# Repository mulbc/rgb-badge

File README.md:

<!-- SPDX-License-Identifier: CERN-OHL-S-2.0 -->

**2026-11-20 selected — 22 opens:** The [additive PAIR03 supply join](docs/development/pair03-supply-routing-2026-11-20.md) preserves all 211 previous groups and all 19,349 existing copper items, with GND197/VLED39/USB32. Matching native/physical counts, exact original 104 findings, stable independent replays, byte-exact inverse/nine zone XORs, 32 fault rejections, eight hole controls, 43 source checks and native visual review pass. Use `led-pair03-supply-routing-trial-114mm`. Zero opens and all qualification/Gate A holds remain unfinished; fabrication is prohibited.

**2026-11-24 continuation — selected source remains22 opens:** The [front row-cell discovery](docs/development/front-row-cell-discovery-2026-11-24.md) preserves a repository-replayable three-part cell and independently restored selector. Its21-open RAM state still splits ROW04 and is explicitly unselected. Actual-contact and alternate-placement escapes continue; no successor PCB or fabrication release is selected.

**2026-11-20 selected — 23 opens:** The [PAIR01 supply continuation](docs/development/pair01-supply-routing-2026-11-20.md) joins PAIR01.4 to main VLED38, preserving all 212 prior groups, main GND197 and retained attached copper. Native and physical counts match at23 with exact original104. Replays, byte-exact inverse/all nine zone XORs, 43 fault/hole/courtyard controls, 42 source checks and native visual review pass. Use `led-pair01-supply-routing-trial-114mm`. Zero opens and all qualification/Gate A holds remain unfinished; fabrication is prohibited.

**2026-11-20 selected — 24 opens:** The [R6 direct bottom continuation](docs/development/r6-direct-bottom-routing-2026-11-20.md) preserves all 213 prior groups, all 197 main ground pads, all 37 main VLED pads and attached retained copper. Native and physical counts match at 24 with exact original104. Replays, byte-exact inverse/all nine zone XORs, 43 fault/hole/courtyard controls, 41 source checks and native visual review pass. Use `led-r6-direct-bottom-trial-114mm`. Zero opens and all qualification/Gate A holds remain unfinished; fabrication is prohibited.

**2026-11-19 selected — 27 opens:** The [minimal R21 supply join](docs/development/r21-routing-2026-11-19.md) preserves all 216 prior groups and attached source copper, with 27 matching native/physical opens and exact original104. Exact replays/inverse, serialized-source guards, 28 fault rejections, eight hole controls, 38 source checks and native visual review pass. Use `led-r21-routing-trial-114mm`; the zero-open goal and all qualification/Gate A holds remain unfinished. Fabrication is prohibited.

**2026-11-15 selected — 29 opens:** The [inverter clock join](docs/development/inverter-routing-2026-11-15.md) localizes exact U48/C67 and joins U48.4–U49.7. All 218 prior groups survive. Native/physical 29 opens, exact original 104 findings under independent U48/prior U52 transforms, two byte-identical replays, byte-identical inverse reconstruction, 18 fault guards, eight hole-policy controls, 36 source checks and visual review pass. Use `led-inverter-routing-trial-114mm`. Zero opens and all electrical/part/process/fit/stack/Gate A holds remain; fabrication is prohibited.

**2026-11-14 selected — 30 opens:** The [complete enable join](docs/development/enable-routing-2026-11-14.md) closes the five-terminal DISPLAY_ENABLE group with one exact C71 shift and two private-leaf replacements. All 219 prior groups survive. Native/physical 30 opens, exact original 104 findings under the unchanged prior pose transform, stable independent replays, inverse-source proof, 18 fault guards, 35 source checks and native visual review pass. Use `led-enable-routing-trial-114mm`. Zero opens and all electrical/part/process/fit/stack/Gate A holds remain; fabrication is prohibited.

**2026-11-14 selected — 31 opens:** The [clear-output join](docs/development/clear-output-routing-2026-11-14.md) connects U52.4 to U49.2/R108.1 through ordinary-width copper. All 220 prior groups and 19,226 source copper items survive. Native/physical 31 opens, exact original 104 finding payloads under the existing frozen pose transform, independent stable replays, byte-identical source restoration, eleven native faults, 34 source checks and native visual review pass. Use `led-ordinary-routing-trial-114mm`. Zero opens and electrical/part/process/fit/stack/Gate A acceptance remain unresolved; fabrication is prohibited.

**2026-11-14 selected — 32 opens:** The [complete control cluster](docs/development/control-cluster-routing-2026-11-14.md) joins U51.4–U52.1 with exact U52/C71 placement and bounded loop/row replacements. All 221 original groups survive, with 32 native/physical opens, the original 104 finding payloads under the exact U52 pose transform, stable byte-identical replays, inverse-source proof, 18 fault guards, 33 source checks and native visual review. Use `led-control-cluster-routing-trial-114mm`. Zero opens, electrical/part/process/fit/stack qualification and independent Gate A remain open; fabrication is prohibited.

**2026-11-12 selected — 33 opens:** The [gauge-supply join](docs/development/gauge-supply-routing-2026-11-12.md) adds exact ordinary-width copper, preserving every prior group and source item. Native/physical 33 opens, exact unchanged 104 findings, stable byte-identical replays, eleven native faults, 32 source checks and visual review pass. Use `led-gauge-routing-trial-114mm`. U35 supply, zero opens and electrical/process/fit/stack/Gate A acceptance remain open; fabrication is prohibited.

**2026-11-12 selected — 34 opens:** The [USB EN1 join](docs/development/usb-en1-routing-2026-11-12.md) localizes exact R70/TP31 and joins U23.4, preserving every prior group and all other copper with no new vias. Exact unchanged 104 findings, stable independent replays, 12 native faults, 31 source checks and visual review pass. Use `led-usb-en1-routing-trial-114mm`; the corrected RSE parent stays immutable. Zero opens and electrical/process/fit/stack/Gate A acceptance remain open; fabrication is prohibited.

**2026-11-12 corrected routing source — 35 opens:** The [RSE pin correction](docs/development/rse-pin-correction-2026-11-12.md) fixes U49/U50 physical pin assignments, restores all 223 prior functional groups and preserves all previous accepted additions. Exact unchanged 104 findings, independent stable replays, native/source/fault and visual checks pass. Continue from `led-rse-corrected-routing-trial-114mm`; preceding boards retain the historical wrong map. Zero opens, electrical/process/fit/stack qualification and independent Gate A remain open; fabrication is prohibited.

**2026-11-07 switch routing selected — 43 opens:** The [validated successor](docs/development/switch-routing-2026-11-07.md) joins SW2.3–R83.1–U36.5, retains all 232 immutable 44-open parent groups and every prior copper item, and passes exact unchanged 104-finding DRC, stable replay/fills, source/orphan/fault and visual checks. The zero-open goal remains in progress. Added supply bridges, controlled stack, 557 historical centre microvias, electrical/process/fit qualification and independent Gate A remain open; fabrication is prohibited.

**2026-11-09 remaining routing selected — 36 opens:** The [validated successor](docs/development/remaining-routing-2026-11-07.md) shifts exact C32 upward by 0.250 mm, retaining its supply contact and joining its ground island through one filled B.Cu component. No copper is added or retired by this step. All 225 preceding groups and 226 additions, plus all 231 immutable parent groups, survive. Exact unchanged 104-finding DRC, stable replay/fills, 36 fault guards, 27 source checks and native visual review pass. The zero-open goal, electrical/thermal/stack/process/fit qualification, 557 historical centre vias and independent Gate A remain open; fabrication is prohibited.
# RGB Badge

An open-source, full-colour wearable LED badge inspired by the FOSSASIA Badge Magic form factor.

The project is currently in **draft schematic development**. Several coupon circuits are captured, including a provisional charger core, but the complete power circuit and PCB are unfinished. No board in this repository has been independently reviewed, fabricated or tested. Do not treat current design material as production-ready.

The current [30-open CAD study](docs/development/enable-routing-2026-11-14.md) retains 104 inventoried intrinsic findings. Circuit completion, electrical/process/fit/stack qualification and independent Gate A review remain open.

## Product target

| Property | Target |
|---|---:|
| Display | 48 × 16 individually controlled RGB pixels |
| Pixel pitch | 1.95 mm |
| Finished envelope | ≤118 × 35 × 11 mm working limit; 114 × 32.5 mm PCB target |
| Finished weight | ≤75 g target; 100 g absolute maximum |
| Reference runtime | Approximately 6 h at the defined mixed-content workload and fixed indoor brightness |
| Charging/data | USB-C, 5 V, A-to-C and C-to-C; native USB data |
| Wireless | BLE enabled only in programming mode |
| Controller | ESP32-S3-WROOM-1U-N16R8 |
| Manufacturing | Turnkey PCBA; no hand assembly of SMT parts |

Six hours is not a maximum-brightness guarantee. The initial model predicts about 6.3 hours with a 900 mAh cell for the reference workload and about 1.1 hours for continuous maximum full-screen white. Coupon measurements will replace those estimates.

## Development strategy

The first physical board is a production-intent 16 × 16 coupon. It compares Everlight `EAST10105RGBA0` 1010 and QT Brightek `QBLP1515A-RGB2A` 1515 common-anode RGB LEDs while exercising the intended controller, matrix driver, USB-C, charger, battery gauge, power converters, antenna and controls. The full 48 × 16 badge will not be ordered until the coupon passes its electrical, optical, thermal, runtime and RF acceptance tests.

For coupon routing, [ADR 0034](docs/decisions/0034-uniform-qt-coupon-pitch-proposal.md) sets the 1515 half to 2.2 mm horizontal / 1.95 mm vertical pitch and uniform orientation; the 1010 half stays at 1.95 mm in both axes. The final badge still targets no more than 1.95 mm in either axis, so coupon optical comparisons must account for the different spacing.

Start with:

1. [Project context](CONTEXT.md)
2. [Requirements](docs/requirements.md)
3. [Full project plan](docs/project-plan.md)
4. [Accepted decisions](docs/decisions/README.md)
5. [Coupon core component candidates](docs/sourcing/coupon-rev-a-core-candidates.md)
6. [Contributor and agent rules](AGENTS.md)

## Repository layout

| Path | Contents |
|---|---|
| `docs/` | Requirements, decisions, project plan, bring-up and test evidence |
| `hardware/` | Editable KiCad projects and project-local libraries |
| `firmware/` | ESP-IDF firmware and host-side tests |
| `mechanical/` | Parametric enclosure source and reviewed exports |
| `manufacturing/` | Immutable, revisioned fabrication and assembly releases |
| `tools/` | Asset compiler, validation and release tooling |

## Safety and verification

This project contains a rechargeable lithium-polymer cell and switching power electronics. A completed coupon schematic and preliminary PCB layout must be reviewed by an experienced hardware engineer before fabrication. Battery charge limits may only be changed after checking the exact terminated-pack specification. Test results must always identify the board revision and must never be inferred or fabricated.

## Attribution

The project uses the [FOSSASIA Badge Magic hardware](https://github.com/fossasia/badgemagic-hardware) as an attributed reference. It is a new design rather than a copy of that PCB. See [NOTICE](NOTICE).

## Licensing

- Hardware design files, mechanical design files, manufacturing files and hardware documentation: [CERN-OHL-S-2.0](LICENSES/CERN-OHL-S-2.0.txt).
- Firmware, scripts and software tooling: [Apache-2.0](LICENSES/Apache-2.0.txt).
- Third-party files retain their original licences and must be recorded before inclusion.

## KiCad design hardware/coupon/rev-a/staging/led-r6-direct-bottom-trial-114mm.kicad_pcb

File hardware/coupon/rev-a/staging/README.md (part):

<!-- SPDX-License-Identifier: CERN-OHL-S-2.0 -->

**2026-11-15 selected — 28 opens:** The [complete row-two exchange](../../../../docs/development/row2-routing-2026-11-15.md) moves exact R8/R37, joins the full ROW_GATE_02 and restores all selector/ground contacts. All 217 prior groups survive, with matching native/physical counts and exact original 104 findings. Two byte-identical replays, byte-identical inverse, 21 fault guards, eight hole controls, 37 source checks and native visual review pass. Use `led-row2-routing-trial-114mm`. Zero opens and all electrical/part/process/fit/stack/Gate A holds remain; fabrication is prohibited.

Current routed derivative: [58-edge source with printed switch terminals](led-routing-progress-trial-114mm.kicad_pcb). The [source record](../../../../docs/development/led-routing-progress-58-study-2026-10-30.md) preserves all earlier physical groups/copper/poses and the 104 intrinsic findings, corrects the second-pole labels without moving contacts, and adds the exact gauge-switch supply join. Run `./tools/check-routing-progress.sh`. Inductor locality, electrical/assembly qualification and independent Gate A remain open; fabrication is prohibited.

Historical routed derivative: [native-clearance gate/control continuation](../../../../docs/development/led-native-control-study-2026-10-21.md)
records nineteen joins and exact retirement of twenty-five source tracks/four vias across ROW_SEL_04/COL_07_R/COL_06_G/COL_02_G, with
no placement changes, leaving 215 native opens and the
same 104 intrinsic DRC findings. Run `./tools/check-native-control.sh` from the
repository root. All prior physical pad groups survive; electrical/process/fit
qualification and Gate A remain open. Never fabricate from this study.

Preceding routed derivative: [row-13 bias study](../../../../docs/development/led-row13-bias-study-2026-10-21.md)
moves R19 and joins its gate/VLED terminals, leaving 234 native opens and the
same 104 intrinsic DRC findings. Existing copper and pad groups survive; nine
gate-side pullups connect. Run `./tools/check-row13-bias.sh` from the repository
root. This mixed-source, unbuilt study is never fabrication source.

# Coupon staging and layout studies

**Historical combined routing study:** The [guarded control continuation](led-control-continuation-trial-114mm.kicad_pcb) has 236 native opens and exactly 104 unchanged intrinsic DRC findings. [Evidence](../../../../docs/development/led-control-continuation-study-2026-10-21.md) records ten joins, preserved existing physical pad groups and rollback of plane-splitting routes. Run `./tools/check-control-continuation.sh` from the repository root. No component, current setting or display-output boundary changes; this unbuilt mixed-source study is never fabrication source.

**Previous physical-drain checkpoint:** [Both physical row-drain lands](led-row-drain-tie-trial-114mm.kicad_pcb) are now joined on all sixteen pairs. [Evidence](../../../../docs/development/led-row-drain-tie-study-2026-10-20.md) records 246 native opens, unchanged source tracks/placements/other pad clusters, exactly 104 intrinsic DRC findings, deterministic regeneration and a negative missing-tie test. Run `./tools/check-row-drain-tie.sh` from the repository root. This unbuilt mixed-source study is never fabrication source.

The separate [VLED converter candidate](../vled-converter-capture-contract.md) now stages thirteen exact-MPN items in vled-converter.kicad_sch. It is default-disabled and remains unlinked until protected SYS and the hardware display interlock are captured.

The separate [VLED local layout trial](vled-layout-trial.kicad_pcb) uses the same thirteen project-local footprints and their exported schematic pad nets at the coordinates of the [lower-right cluster screen](../../../../mechanical/dual-row-package-screen-2026-10-06.md). It has a local study outline, no tracks, vias or copper zones, and none of the neighbouring final-board circuitry. Generate and round-trip-check it with KiCad's bundled Python: `/Applications/KiCad/KiCad.app/Contents/Frameworks/Python.framework/Versions/3.9/bin/python3 tools/generate-vled-layout-trial.py`. KiCad 10.0.6 loaded and plotted its actual pads. [Native local-board DRC evidence](../../../../docs/development/vled-layout-trial-2026-10-06.md) records zero geometric violations and thirty expected open connections when run with desktop access. This is not a routed/full-board DRC pass. This file is a placement study, never a fabrication source.

The separate [display-interlock placement trial](display-interlock-layout-trial.kicad_pcb) groups the 31 captured interlock footprints and carries their exported pad nets. Generate it with KiCad's bundled Python using `tools/generate-display-interlock-layout-trial.py`. [Native DRC findings](../../../../docs/development/display-interlock-layout-trial-2026-10-13.md) show eight intra-footprint clearance violations at the present 0.20 mm rule and 76 expected unrouted connections. It has no routed/full-board DRC pass and is never a fabrication source.

The [full-footprint 120 mm coupon trial](full-coupon-placement-trial-120mm.kicad_pcb) stages every captured footprint and native pad net on two faces of a provisional six-layer board while retaining all 32 current row transistors. The linked study paths include four E0/E1 support nets, both J1 VBUS pads to E0/C60, E0-to-C61, E1-to-C52, C52-to-U41/C56, the local R93 ILIM/ground loop, C62/C57 timing-capacitor and both eFuse IC ground returns, the second J1 GND contact, E1 pad 2, two U37-to-L2 switching nets and 16 Everlight half-row anode trunks. Nearly all other routing remains open. Its [source and DRC record](../../../../docs/development/full-coupon-placement-trial-2026-10-13.md) explains why this larger board is a layout discovery artifact, not the accepted 110 mm badge PCB or a release output.

The separate [red-column HDI trial](red-column-hdi-trial-120mm.kicad_pcb) copies that full-footprint study and adds tentative pad-centred F.Cu–In1.Cu microvias for all sixteen red cathode columns. [Its review](../../../../docs/development/red-column-hdi-screen-2026-10-14.md) records native DRC and the still-open green/blue routing and manufacturing process. Generate it with `tools/generate-red-column-hdi-trial.py`; it is not the canonical PCB or a fabrication source.

The [114 mm grouped placement study](paired-charger-placement-only-114mm.kicad_pcb) uses actual KiCad pads for the provisional paired-row and charger-group XY option, with two projected final drivers and TH1/U39 fixed in the battery-facing central sensor reservation. It is unrouted and the row-pair/extra-driver pads are netless. [Its native DRC record](../../../../docs/development/paired-charger-114mm-placement-study-2026-10-14.md) identifies 104 known fine-pitch pad-gap violations and a capped unconnected listing; it does not approve the row substitution, sensor thermal coupling, enclosure fit or fabrication. Generate it with `tools/generate-paired-charger-114mm-placement.py` using KiCad's bundled Python.

The separate [114 mm local routing trial](paired-charger-local-routing-trial-114mm.kicad_pcb) connects five BQ24074 support nets, stages three USB-to-charger rail segments (J1 to E0, E0 to E1, E1 to BQ IN) and joins a partial local ground tree. [Its native DRC record](../../../../docs/development/paired-charger-114mm-local-routing-2026-10-14.md) retains the same 104 intrinsic pad-gap findings. The 0.20 mm traces are not qualified for charger/system current, and almost all nets remain open. Generate it with `tools/generate-paired-charger-114mm-routing.py` using KiCad's bundled Python.

`3v3-converter.kicad_sch` contains the exact `TPS631000DRLR`, one Murata `DFE252012P-1R0M=P2` 1 µH inductor, two `GRM187R61A226ME15` input capacitors, two `GRM219R60J476ME44` output capacitors, the Panasonic 511 kΩ / 91 kΩ feedback pair, and a 100 kΩ EN pull-down. The source checker verifies nine items, all 24 pins and the two *local* LX switching nodes. Regenerate deterministically into a new directory with `python3 tools/generate-coupon-3v3.py --output /tmp/rgb-3v3-candidate`; compare with this source before replacing it.

This historical candidate remains **unlinked** for deterministic comparison. A distinct, root-linked copy now exists at `../3v3-converter.kicad_sch` with SW2's first control pole on EN; the previous `+3V3_APP` draft source flag was removed. `+SYS_APP_IN_DRAFT` remains a flagged, unresolved charger/pack source. `APP_3V3_FB` is a schematic feedback net, not a routed board design. The battery pack, charger, gauge pole, LED supply and whole-board OFF leakage remain uncaptured or unqualified.

The [capture contract](../3v3-converter-capture-contract.md) records the TI starting circuit, conditional capacitor choice and load/current sensitivity. The [inductor audit](../3v3-inductor-footprint-audit.md) and capacitor/feedback audits control the libraries. [Native XML and visual review at c929711](../../../../docs/development/3v3-candidate-review-c929711.md) confirms all 24 connections and identifies two presentation repairs, now source-corrected but awaiting the next combined export. No candidate ERC report was supplied; the main project's passing ERC does not validate it. Integrate only after the protected SYS and switch boundaries are reviewed, then remove the superseded flags, run native ERC/netlist and inspect the page, and update the whole-project checker. This is not a fabrication release.

The [combined-board ground-escape candidate](led-ground-escape-trial-114mm.kicad_pcb) adds rear-pad escapes and an In2 GND pour to the combined row-control derivative. [Its evidence and limitations](../../../../docs/development/led-ground-escape-study-2026-10-20.md) record 383 native open edges, six ground regions, unchanged non-ground connectivity and a passing native shape-clearance screen. **Full native DRC completed with desktop access: exactly 104 unchanged intrinsic footprint-clearance findings.** Run `./tools/check-ground-escape.sh` from the repository root for full acceptance. It is never fabrication source.

The [combined-board ground-return derivative](led-ground-return-trial-114mm.kicad_pcb) retains the checked ground escapes and adds rear GND copper plus four targeted joins. [Its native evidence](../../../../docs/development/led-ground-return-study-2026-10-20.md) records 366 total opens, 27 GND opens, exactly 104 unchanged intrinsic DRC findings, unchanged components/non-ground clusters and byte-identical regeneration. Repeat full acceptance with `./tools/check-ground-return.sh` from the repository root. Ground and other routing, RF/thermal/process qualification and independent Gate A remain incomplete; it is never fabrication source.

The [local row-14 bias derivative](led-row14-bias-trial-114mm.kicad_pcb) moves R20 beside PAIR15 and connects both its gate and local VLED terminals. [Native evidence](../../../../docs/development/led-row14-bias-study-2026-10-20.md) records 364 full opens, eight connected gate pullups and exactly 104 unchanged DRC findings. All other components/clusters and source tracks survive; GND still has 27 opens. It is never fabrication source.

The preceding local-control derivative is [local control routing](led-local-control-trial-114mm.kicad_pcb). [Its evidence](../../../../docs/development/led-local-control-study-2026-10-20.md) records ten control joins, 354 full native opens and exactly 104 unchanged intrinsic DRC findings. It preserves all prior placements, tracks/vias and connected pad clusters, including the incomplete ground returns. Repeat full study acceptance with `./tools/check-local-control.sh`. Remaining supplies, eight pullups, HDI/electrical/mechanical qualification and Gate A remain open; it is never fabrication source.

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
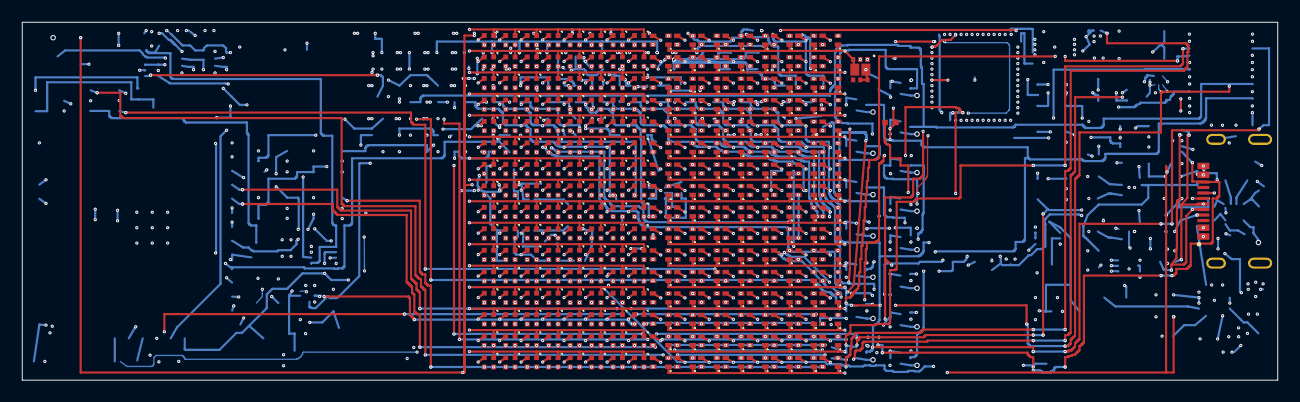
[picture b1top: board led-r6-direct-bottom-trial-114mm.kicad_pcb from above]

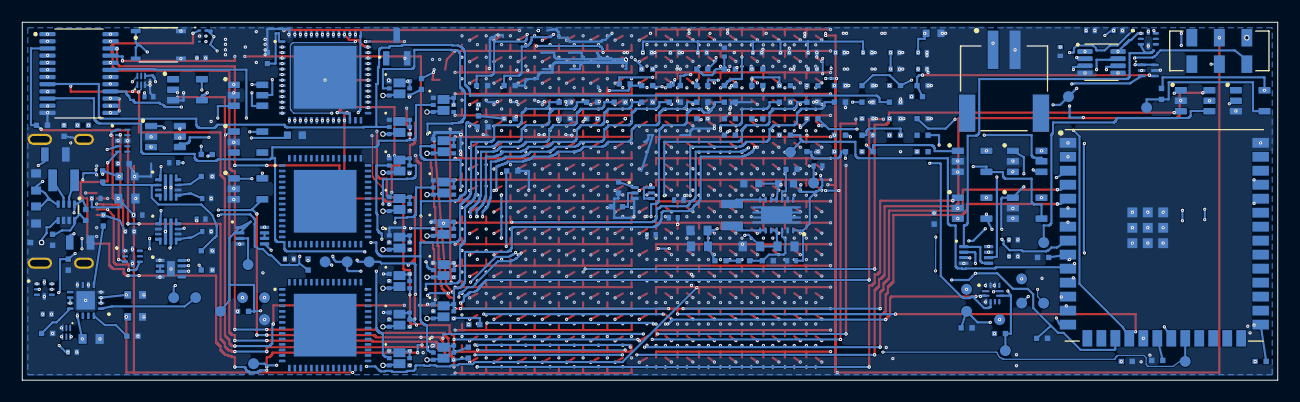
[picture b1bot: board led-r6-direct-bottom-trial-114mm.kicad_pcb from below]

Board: 6 copper layers, 114.0 x 32.5 mm, 483 parts (224 on the bottom side), 188 nets.

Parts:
C1, C2, C4, C11, C17, C23, C24, C25, C36, C37, C38, C39, C50, C51, C55, C58, C59, C63, C64, C65, C66, C67, C68, C69, C70, C71, C72, C73, C74: 100n 16V X7R; C_Murata_GRM15_0402
C3, C32, C44, C45, C53, C54: 10u 6.3V X5R; C_Murata_GRM188R60J106ME47_0603
C5, C30, C31, C52: 1u 10V X7S; C_Murata_GRM15_0402
C40, C41, C46, C47, C48, C49, C56, C61: 22u 10V X5R; C_Murata_GRM187R61A226ME15_0603
C42, C43: 47u 6.3V X5R; C_Murata_GRM219R60J476ME44_0805
C57, C62: 2.2n 50V C0G; C_Murata_GRM15_0402
C60: 1u 50V X7R; C_TDK_C1608_0603
D1, D2, D3, D4, D5, D6, D7, D8, D17, D18, D19, D20, D21, D22, D23, D24, D33, D34, D35, D36, D37, D38, D39, D40, D49, D50, D51, D52, D53, D54, D55, D56, D65, D66, D67, D68, D69, D70, D71, D72, D81, D82, D83, D84, D85, D86, D87, D88, D97, D98, D99, D100, D101, D102, D103, D104, D113, D114, D115, D116, D117, D118, D119, D120, D129, D130, D131, D132, D133, D134, D135, D136, D145, D146, D147, D148, D149, D150, D151, D152, D161, D162, D163, D164, D165, D166, D167, D168, D177, D178, D179, D180, D181, D182, D183, D184, D193, D194, D195, D196, D197, D198, D199, D200, D209, D210, D211, D212, D213, D214, D215, D216, D225, D226, D227, D228, D229, D230, D231, D232, D241, D242, D243, D244, D245, D246, D247, D248: EAST10105RGBA0; LED_Everlight_EAST10105RGBA0
D9, D10, D11, D12, D13, D14, D15, D16, D25, D26, D27, D28, D29, D30, D31, D32, D41, D42, D43, D44, D45, D46, D47, D48, D57, D58, D59, D60, D61, D62, D63, D64, D73, D74, D75, D76, D77, D78, D79, D80, D89, D90, D91, D92, D93, D94, D95, D96, D105, D106, D107, D108, D109, D110, D111, D112, D121, D122, D123, D124, D125, D126, D127, D128, D137, D138, D139, D140, D141, D142, D143, D144, D153, D154, D155, D156, D157, D158, D159, D160, D169, D170, D171, D172, D173, D174, D175, D176, D185, D186, D187, D188, D189, D190, D191, D192, D201, D202, D203, D204, D205, D206, D207, D208, D217, D218, D219, D220, D221, D222, D223, D224, D233, D234, D235, D236, D237, D238, D239, D240, D249, D250, D251, D252, D253, D254, D255, D256: QBLP1515A-RGB2A; LED_QTBrightek_QBLP1515A-RGB2A
J1: USB4505-03-0-A; USB_C_GCT_USB4505-03-0-A_MidMount
J2: S2B-PH-SM4-TB; JST_PH_S2B-PH-SM4-TB
L1: 1u 20%; L_Murata_DFE252012P
L2: 1.5u 20%; L_Murata_DFE252012P
PAIR01, PAIR02, PAIR03, PAIR04, PAIR05, PAIR06, PAIR07, PAIR08, PAIR09, PAIR10, PAIR11, PAIR12, PAIR13, PAIR14, PAIR15, PAIR16: NTLJD3119CTBG_TRIAL_ONLY; WDFN6_2x2_onsemi_NTLJD3119C
PROJ_U1_2, PROJ_U1_3: PROJECTED_DRIVER_GEOMETRY_ONLY; QFN_TI_RTQ0056E_8x8mm_P0.5mm_EP5.7mm
R1: 39.2k 1%; R_Panasonic_ERJ2_0402
R2, R3, R4, R5, R22, R23, R24, R25, R26, R27, R28, R29, R30, R31, R32, R33, R34, R35, R36, R37, R38, R39, R40, R41, R42, R62, R76, R77, R78, R83, R87: 100k 1%; R_Panasonic_ERJ2_0402
R6, R7, R8, R9, R10, R11, R12, R13, R14, R15, R16, R17, R18, R19, R20, R21: 1k 1%; R_Panasonic_ERJ2_0402
R43, R44, R60, R61, R70, R88, R91, R98: 10k 1%; R_Panasonic_ERJ2_0402
R45, R46: 22R 1%; R_Panasonic_ERJ2_0402
R47: 499R 1%; R_Panasonic_ERJ2_0402
R63: 1M 1%; R_Panasonic_ERJ2_0402
R71: 887k 1%; R_Panasonic_ERJ2_0402
R75, R84, R85: 620k 1%; R_Panasonic_ERJ2_0402
R79, R80, R101, R102: 2.2k 1%; R_Panasonic_ERJ2_0402
R81: 511k 1%; R_Panasonic_ERJ2_0402
R82: 91k 1%; R_Panasonic_ERJ2_0402
R86: 180k 1%; R_Panasonic_ERJ2_0402
R89: 2.15k 1%; R_Panasonic_ERJ2_0402
R90: 14k 1%; R_Panasonic_ERJ2_0402
R92: 2.49k 0.1%; R_Panasonic_ERA2_0402
R93: 3.65k 0.1%; R_Panasonic_ERA2_0402
R94: 220k 1%; R_Panasonic_ERJ2_0402
R95: 270k 1%; R_Panasonic_ERJ2_0402
R96, R100: 3.32k 1%; R_Panasonic_ERJ2_0402
R97: 38.3k 1%; R_Panasonic_ERJ2_0402
R99: 390k 1%; R_Panasonic_ERJ2_0402
R103: ERJ2RKF1001X; R_Panasonic_ERJ2_0402
R104, R105, R106: ERJ2RKF1002X; R_Panasonic_ERJ2_0402
R107, R108: ERJ2RKF1003X; R_Panasonic_ERJ2_0402
R109: ERJ2RKF1603X; R_Panasonic_ERJ2_0402
R110, R112: ERJ2RKF2002X; R_Panasonic_ERJ2_0402
R111: ERJ2RKF1963X; R_Panasonic_ERJ2_0402
R113: ERJ2RKF4701X; R_Panasonic_ERJ2_0402
SW1: EVQP7J01P; SW_Panasonic_EVQP7J01P
SW2: JS202011JCQN; SW_CK_JS202011JCQN_ManufacturerPins
TH1: 10k NTC; NTC_Murata_NCU15_0402
TP1: LED_SOUT; TestPoint_Pad_D1.0mm
TP2, TP3, TP4, TP5, TP6, TP7, TP8, TP9, TP10, TP11, TP12, TP13, TP14, TP34, TP35: TestPoint_Pad; TestPoint_Pad_D1.0mm
TP20: OUT1; TestPoint_Pad_D1.0mm
TP21: OUT2; TestPoint_Pad_D1.0mm
TP22: VBUS_VALID; TestPoint_Pad_D1.0mm
TP23: LOGIC_READY; TestPoint_Pad_D1.0mm
TP30: CHARGE_REQ; TestPoint_Pad_D1.0mm
TP31: EN1_RAW_N; TestPoint_Pad_D1.0mm
TP32: VBUS_CONNECTOR; TestPoint_Pad_D1.0mm
TP33: 5V_USB_BOUNDARY; TestPoint_Pad_D1.0mm
U1: TLC59581RTQT; QFN_TI_RTQ0056E_8x8mm_P0.5mm_EP5.7mm
U2: 74HC4514PW,118; TSSOP_Nexperia_SOT355-1_24
U3: ESP32-S3-WROOM-1U-N16R8; ESP32-S3-WROOM-1U
U11: SN74LVC1G04DBVR; SOT23_TI_DBV0005A
U17: SN74LVC1G11DBVR; SOT23_TI_DBV0006A
U23: SN74LVC1G06DBVR; SOT23_TI_DBV0005A
U24, U25: SN74LVC2G17DBVR; SOT23_TI_DBV0006A
U29: TPS70933DBVR; SOT23_TI_DBV0005A
U31: TUSB320LAIRWBR; X2QFN_TI_RWB0012A_1.6x1.6mm_P0.4mm
U32: TS3USB31ERSER; UQFN_TI_RSE0008A_1.5x1.5mm_P0.5mm
U33: TPD4E05U06DQAR; USON_TI_DQA0010A
U34: TPS3808G01DBVR; SOT23_TI_DBV0006A
U35: MAX17048G+T10; TDFN_Maxim_T822-3_2x2mm_P0.5mm_EP0.7x1.38mm
U36: TPS631000DRLR; SOT5X3_TI_DRL0008A
U37: TPS63020DSJT; VSON_TI_DSJ0014_4x3mm_P0.5mm_EP2.85x1.58mm
U38: 2.5V shunt; SOT23_TI_DBZ0003A
U39: TMP390A2DRLR; SOT563_TI_DRL0006A
U40, U42, U43: SN74AUP1G125DBVR; SOT23_TI_DBV0005A
U41: BQ24074RGTR; VQFN_TI_RGT0016C_3x3mm_P0.5mm_EP1.68mm
U44, U45: TPS259474ARPWR; VQFN_TI_RPW0010A_2x2mm_HotRod
U46: TCA9517ADGKR; VSSOP_TI_DGK0008A
U47: TPS3823A-33DBVR; SOT23_TI_DBV0005A
U48: SN74LVC1G04DSFR; X2SON_TI_DSF0006A_1x1mm_P0.35mm
U49, U50: SN74LVC1G74RSER; UQFN_TI_RSE0008A_1.5x1.5mm_P0.5mm
U51: SN74LVC1G11DRYR; USON_TI_DRY0006A_1p45x1mm_P0p5mm
U52: SN74LVC1G08DSFR; X2SON_TI_DSF0006A_1x1mm_P0.35mm
U53: TLV6700DSER; WSON_TI_DSE0006A_1p5x1p5mm_P0p5mm
U54: SN74LVC2G00DCUR; VSSOP_TI_DCU0008A
U55: SN74LVC2G08DCUR; VSSOP_TI_DCU0008A

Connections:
+3V3_APP: C1.1, C2.1, C3.1, C4.1, C37.1, C42.1, C43.1, C65.1, C66.1, C67.1, C68.1, C69.1, C70.1, C71.1, C72.1, C73.1, C74.1, R42.1, R43.1, R44.1, R79.1, R80.1, R81.1, R104.1, R106.1, TP8.1, U1.43, U2.1, U2.24, U3.2, U32.8, U36.1, U46.5, U46.8, U47.3, U47.5, U48.6, U49.1, U49.6, U49.8, U50.1, U50.8, U51.5, U52.6, U53.2, U54.8, U55.8
+3V3_USB: C11.1, C17.1, C23.1, C24.1, C25.1, C32.1, C36.1, C38.1, C50.1, C51.1, C58.1, C59.1, R60.2, R61.2, R70.1, R75.1, R77.1, R78.1, R91.1, R94.1, U11.5, U17.5, U23.5, U24.5, U25.5, U29.5, U31.12, U34.3, U34.6, U39.5, U40.5, U42.5, U43.5
+5V_USB: C30.1, C31.1, C55.1, C61.1, TP33.1, U29.1, U44.5, U45.6
+BAT_GAUGE_SW: C39.1, C64.1, R101.1, R102.1, SW2.7, U35.2, U35.3, U46.1
+BAT_PROTECTED_DRAFT: C53.1, J2.1, SW2.6, U41.2, U41.3
+SYS_APP_IN_DRAFT: C40.1, C41.1, C44.1, C45.1, C54.1, C63.1, SW2.2, U36.4, U37.1, U37.10, U37.11, U41.10, U41.11
APP_3V3_FB: R81.2, R82.1, U36.8
APP_ON_SW_DRAFT: R83.1, SW2.3, U36.5
APP_SUPERVISOR_OK: U47.1, U51.1
ARM_LATCH: U50.3, U55.1, U55.5
CHARGER_EN2: R88.2, U38.1, U41.5
CHARGER_GATE_EN: R94.2, R95.1, TP35.1, U40.4, U42.4, U43.4, U44.1
CHARGER_ILIM: R93.1, U41.12
CHARGER_IN_DRAFT: C52.1, C56.1, R88.1, U41.13, U44.6
CHARGER_ISET: R92.1, U41.16
CHARGER_TS: TH1.1, TP34.1, U41.1
COL_00_B: D1.3, D17.3, D33.3, D49.3, D65.3, D81.3, D97.3, D113.3, D129.3, D145.3, D161.3, D177.3, D193.3, D209.3, D225.3, D241.3, U1.10
COL_00_G: D1.4, D17.4, D33.4, D49.4, D65.4, D81.4, D97.4, D113.4, D129.4, D145.4, D161.4, D177.4, D193.4, D209.4, D225.4, D241.4, U1.9
COL_00_R: D1.2, D17.2, D33.2, D49.2, D65.2, D81.2, D97.2, D113.2, D129.2, D145.2, D161.2, D177.2, D193.2, D209.2, D225.2, D241.2, U1.8
COL_01_B: D2.3, D18.3, D34.3, D50.3, D66.3, D82.3, D98.3, D114.3, D130.3, D146.3, D162.3, D178.3, D194.3, D210.3, D226.3, D242.3, U1.13
COL_01_G: D2.4, D18.4, D34.4, D50.4, D66.4, D82.4, D98.4, D114.4, D130.4, D146.4, D162.4, D178.4, D194.4, D210.4, D226.4, D242.4, U1.12
COL_01_R: D2.2, D18.2, D34.2, D50.2, D66.2, D82.2, D98.2, D114.2, D130.2, D146.2, D162.2, D178.2, D194.2, D210.2, D226.2, D242.2, U1.11
COL_02_B: D3.3, D19.3, D35.3, D51.3, D67.3, D83.3, D99.3, D115.3, D131.3, D147.3, D163.3, D179.3, D195.3, D211.3, D227.3, D243.3, U1.16
COL_02_G: D3.4, D19.4, D35.4, D51.4, D67.4, D83.4, D99.4, D115.4, D131.4, D147.4, D163.4, D179.4, D195.4, D211.4, D227.4, D243.4, U1.15
COL_02_R: D3.2, D19.2, D35.2, D51.2, D67.2, D83.2, D99.2, D115.2, D131.2, D147.2, D163.2, D179.2, D195.2, D211.2, D227.2, D243.2, U1.14
COL_03_B: D4.3, D20.3, D36.3, D52.3, D68.3, D84.3, D100.3, D116.3, D132.3, D148.3, D164.3, D180.3, D196.3, D212.3, D228.3, D244.3, U1.19
COL_03_G: D4.4, D20.4, D36.4, D52.4, D68.4, D84.4, D100.4, D116.4, D132.4, D148.4, D164.4, D180.4, D196.4, D212.4, D228.4, D244.4, U1.18
COL_03_R: D4.2, D20.2, D36.2, D52.2, D68.2, D84.2, D100.2, D116.2, D132.2, D148.2, D164.2, D180.2, D196.2, D212.2, D228.2, D244.2, U1.17
COL_04_B: D5.3, D21.3, D37.3, D53.3, D69.3, D85.3, D101.3, D117.3, D133.3, D149.3, D165.3, D181.3, D197.3, D213.3, D229.3, D245.3, U1.22
COL_04_G: D5.4, D21.4, D37.4, D53.4, D69.4, D85.4, D101.4, D117.4, D133.4, D149.4, D165.4, D181.4, D197.4, D213.4, D229.4, D245.4, U1.21
COL_04_R: D5.2, D21.2, D37.2, D53.2, D69.2, D85.2, D101.2, D117.2, D133.2, D149.2, D165.2, D181.2, D197.2, D213.2, D229.2, D245.2, U1.20
COL_05_B: D6.3, D22.3, D38.3, D54.3, D70.3, D86.3, D102.3, D118.3, D134.3, D150.3, D166.3, D182.3, D198.3, D214.3, D230.3, D246.3, U1.25
COL_05_G: D6.4, D22.4, D38.4, D54.4, D70.4, D86.4, D102.4, D118.4, D134.4, D150.4, D166.4, D182.4, D198.4, D214.4, D230.4, D246.4, U1.24
COL_05_R: D6.2, D22.2, D38.2, D54.2, D70.2, D86.2, D102.2, D118.2, D134.2, D150.2, D166.2, D182.2, D198.2, D214.2, D230.2, D246.2, U1.23
COL_06_B: D7.3, D23.3, D39.3, D55.3, D71.3, D87.3, D103.3, D119.3, D135.3, D151.3, D167.3, D183.3, D199.3, D215.3, D231.3, D247.3, U1.32
COL_06_G: D7.4, D23.4, D39.4, D55.4, D71.4, D87.4, D103.4, D119.4, D135.4, D151.4, D167.4, D183.4, D199.4, D215.4, D231.4, D247.4, U1.31
COL_06_R: D7.2, D23.2, D39.2, D55.2, D71.2, D87.2, D103.2, D119.2, D135.2, D151.2, D167.2, D183.2, D199.2, D215.2, D231.2, D247.2, U1.30
COL_07_B: D8.3, D24.3, D40.3, D56.3, D72.3, D88.3, D104.3, D120.3, D136.3, D152.3, D168.3, D184.3, D200.3, D216.3, D232.3, D248.3, U1.35
COL_07_G: D8.4, D24.4, D40.4, D56.4, D72.4, D88.4, D104.4, D120.4, D136.4, D152.4, D168.4, D184.4, D200.4, D216.4, D232.4, D248.4, U1.34
COL_07_R: D8.2, D24.2, D40.2, D56.2, D72.2, D88.2, D104.2, D120.2, D136.2, D152.2, D168.2, D184.2, D200.2, D216.2, D232.2, D248.2, U1.33
COL_08_B: D9.2, D25.2, D41.2, D57.2, D73.2, D89.2, D105.2, D121.2, D137.2, D153.2, D169.2, D185.2, D201.2, D217.2, D233.2, D249.2, U1.38
COL_08_G: D9.3, D25.3, D41.3, D57.3, D73.3, D89.3, D105.3, D121.3, D137.3, D153.3, D169.3, D185.3, D201.3, D217.3, D233.3, D249.3, U1.37
COL_08_R: D9.4, D25.4, D41.4, D57.4, D73.4, D89.4, D105.4, D121.4, D137.4, D153.4, D169.4, D185.4, D201.4, D217.4, D233.4, D249.4, U1.36
COL_09_B: D10.2, D26.2, D42.2, D58.2, D74.2, D90.2, D106.2, D122.2, D138.2, D154.2, D170.2, D186.2, D202.2, D218.2, D234.2, D250.2, U1.41
COL_09_G: D10.3, D26.3, D42.3, D58.3, D74.3, D90.3, D106.3, D122.3, D138.3, D154.3, D170.3, D186.3, D202.3, D218.3, D234.3, D250.3, U1.40
COL_09_R: D10.4, D26.4, D42.4, D58.4, D74.4, D90.4, D106.4, D122.4, D138.4, D154.4, D170.4, D186.4, D202.4, D218.4, D234.4, D250.4, U1.39
COL_10_B: D11.2, D27.2, D43.2, D59.2, D75.2, D91.2, D107.2, D123.2, D139.2, D155.2, D171.2, D187.2, D203.2, D219.2, D235.2, D251.2, U1.46
COL_10_G: D11.3, D27.3, D43.3, D59.3, D75.3, D91.3, D107.3, D123.3, D139.3, D155.3, D171.3, D187.3, D203.3, D219.3, D235.3, D251.3, U1.45
COL_10_R: D11.4, D27.4, D43.4, D59.4, D75.4, D91.4, D107.4, D123.4, D139.4, D155.4, D171.4, D187.4, D203.4, D219.4, D235.4, D251.4, U1.44
COL_11_B: D12.2, D28.2, D44.2, D60.2, D76.2, D92.2, D108.2, D124.2, D140.2, D156.2, D172.2, D188.2, D204.2, D220.2, D236.2, D252.2, U1.49
COL_11_G: D12.3, D28.3, D44.3, D60.3, D76.3, D92.3, D108.3, D124.3, D140.3, D156.3, D172.3, D188.3, D204.3, D220.3, D236.3, D252.3, U1.48
COL_11_R: D12.4, D28.4, D44.4, D60.4, D76.4, D92.4, D108.4, D124.4, D140.4, D156.4, D172.4, D188.4, D204.4, D220.4, D236.4, D252.4, U1.47
COL_12_B: D13.2, D29.2, D45.2, D61.2, D77.2, D93.2, D109.2, D125.2, D141.2, D157.2, D173.2, D189.2, D205.2, D221.2, D237.2, D253.2, U1.52
COL_12_G: D13.3, D29.3, D45.3, D61.3, D77.3, D93.3, D109.3, D125.3, D141.3, D157.3, D173.3, D189.3, D205.3, D221.3, D237.3, D253.3, U1.51
COL_12_R: D13.4, D29.4, D45.4, D61.4, D77.4, D93.4, D109.4, D125.4, D141.4, D157.4, D173.4, D189.4, D205.4, D221.4, D237.4, D253.4, U1.50
COL_13_B: D14.2, D30.2, D46.2, D62.2, D78.2, D94.2, D110.2, D126.2, D142.2, D158.2, D174.2, D190.2, D206.2, D222.2, D238.2, D254.2, U1.55
COL_13_G: D14.3, D30.3, D46.3, D62.3, D78.3, D94.3, D110.3, D126.3, D142.3, D158.3, D174.3, D190.3, D206.3, D222.3, D238.3, D254.3, U1.54
COL_13_R: D14.4, D30.4, D46.4, D62.4, D78.4, D94.4, D110.4, D126.4, D142.4, D158.4, D174.4, D190.4, D206.4, D222.4, D238.4, D254.4, U1.53
COL_14_B: D15.2, D31.2, D47.2, D63.2, D79.2, D95.2, D111.2, D127.2, D143.2, D159.2, D175.2, D191.2, D207.2, D223.2, D239.2, D255.2, U1.4
COL_14_G: D15.3, D31.3, D47.3, D63.3, D79.3, D95.3, D111.3, D127.3, D143.3, D159.3, D175.3, D191.3, D207.3, D223.3, D239.3, D255.3, U1.3
COL_14_R: D15.4, D31.4, D47.4, D63.4, D79.4, D95.4, D111.4, D127.4, D143.4, D159.4, D175.4, D191.4, D207.4, D223.4, D239.4, D255.4, U1.2
COL_15_B: D16.2, D32.2, D48.2, D64.2, D80.2, D96.2, D112.2, D128.2, D144.2, D160.2, D176.2, D192.2, D208.2, D224.2, D240.2, D256.2, U1.7
COL_15_G: D16.3, D32.3, D48.3, D64.3, D80.3, D96.3, D112.3, D128.3, D144.3, D160.3, D176.3, D192.3, D208.3, D224.3, D240.3, D256.3, U1.6
COL_15_R: D16.4, D32.4, D48.4, D64.4, D80.4, D96.4, D112.4, D128.4, D144.4, D160.4, D176.4, D192.4, D208.4, D224.4, D240.4, D256.4, U1.5
DISPLAY_ARM_CLK: R107.1, U3.9, U50.7
DISPLAY_CLEAR_3: U51.4, U52.1
DISPLAY_CLEAR_OK: R108.1, U49.2, U50.2, U52.4
DISPLAY_ENABLE: R105.1, TP10.1, U3.17, U52.2, U55.2
DISPLAY_HEARTBEAT: R103.1, U3.8, U47.4, U48.2
E0_DVDT: C62.1, U45.7
E0_EN: R99.2, U45.1
E0_ILM: R100.1, U45.9
E0_OVLO: R97.2, R98.1, U45.2
E1_DVDT: C57.1, U44.7
E1_ILM: R96.1, U44.9
ESP_EN: C5.1, R43.2, TP2.1, U3.3, U51.3
GAUGE_I2C_SCL: R102.2, U35.7, U46.2
GAUGE_I2C_SDA: R101.2, U35.8, U46.3
GND: C1.2, C2.2, C3.2, C4.2, C5.2, C11.2, C17.2, C23.2, C24.2, C25.2, C30.2, C31.2, C32.2, C36.2, C37.2, C38.2, C39.2, C40.2, C41.2, C42.2, C43.2, C44.2, C45.2, C46.2, C47.2, C48.2, C49.2, C50.2, C51.2, C52.2, C53.2, C54.2, C55.2, C56.2, C57.2, C58.2, C59.2, C60.2, C61.2, C62.2, C63.2, C64.2, C65.2, C66.2, C67.2, C68.2, C69.2, C70.2, C71.2, C72.2, C73.2, C74.2, J1.A1_B12, J1.B1_A12, J1.S1, J2.2, PAIR01.1, PAIR02.1, PAIR03.1, PAIR04.1, PAIR05.1, PAIR06.1, PAIR07.1, PAIR08.1, PAIR09.1, PAIR10.1, PAIR11.1, PAIR12.1, PAIR13.1, PAIR14.1, PAIR15.1, PAIR16.1, R1.2, R2.2, R3.2, R4.2, R5.2, R22.2, R23.2, R24.2, R25.2, R26.2, R27.2, R28.2, R29.2, R30.2, R31.2, R32.2, R33.2, R34.2, R35.2, R36.2, R37.2, R38.2, R39.2, R40.2, R41.2, R62.2, R63.2, R76.2, R82.2, R83.2, R86.2, R87.2, R89.2, R90.2, R92.2, R93.2, R95.2, R96.2, R98.2, R100.2, R103.2, R105.2, R107.2, R108.2, R110.2, R112.2, R113.2, SW1.2, TH1.2, TP9.1, U1.56, U1.57, U2.12, U3.1, U3.40, U3.41, U11.3, U17.2, U23.3, U24.2, U25.2, U29.2, U31.3, U31.10, U31.11, U32.1, U32.4, U33.3, U33.8, U34.2, U35.1, U35.4, U35.6, U35.9, U36.6, U36.7, U37.2, U37.13, U37.15, U38.2, U38.3, U39.3, U40.2, U40.3, U41.4, U41.6, U41.8, U41.17, U42.2, U42.3, U43.2, U43.3, U44.2, U44.8, U45.8, U46.4, U47.2, U48.3, U49.4, U50.4, U51.2, U52.3, U53.5, U54.4, U55.4
HEARTBEAT_FALL_CLK: U48.4, U49.7
HEARTBEAT_SEEN: U49.3, U50.6
LED_GCLK: R5.1, TP6.1, U1.29, U3.21
LED_IREF: R1.1, U1.1
LED_LAT: R4.1, U1.27, U3.18
LED_SCLK: R3.1, U1.28, U3.20
LED_SIN: R2.1, U1.26, U3.19
LED_SOUT: TP1.1, U1.42, U3.22
MODE_BOOT_N: R44.2, SW1.1, TP3.1, U3.27, U51.6
unnamed: L2.1, U37.8, U37.9
unnamed: L2.2, U37.6, U37.7
unnamed: L1.1, U36.3
unnamed: L1.2, U36.2
ROW_00_A: D1.1, D2.1, D3.1, D4.1, D5.1, D6.1, D7.1, D8.1, D9.1, D10.1, D11.1, D12.1, D13.1, D14.1, D15.1, D16.1, PAIR01.3
ROW_01_A: D17.1, D18.1, D19.1, D20.1, D21.1, D22.1, D23.1, D24.1, D25.1, D26.1, D27.1, D28.1, D29.1, D30.1, D31.1, D32.1, PAIR02.3
ROW_02_A: D33.1, D34.1, D35.1, D36.1, D37.1, D38.1, D39.1, D40.1, D41.1, D42.1, D43.1, D44.1, D45.1, D46.1, D47.1, D48.1, PAIR03.3
ROW_03_A: D49.1, D50.1, D51.1, D52.1, D53.1, D54.1, D55.1, D56.1, D57.1, D58.1, D59.1, D60.1, D61.1, D62.1, D63.1, D64.1, PAIR04.3
ROW_04_A: D65.1, D66.1, D67.1, D68.1, D69.1, D70.1, D71.1, D72.1, D73.1, D74.1, D75.1, D76.1, D77.1, D78.1, D79.1, D80.1, PAIR05.3
ROW_05_A: D81.1, D82.1, D83.1, D84.1, D85.1, D86.1, D87.1, D88.1, D89.1, D90.1, D91.1, D92.1, D93.1, D94.1, D95.1, D96.1, PAIR06.3
ROW_06_A: D97.1, D98.1, D99.1, D100.1, D101.1, D102.1, D103.1, D104.1, D105.1, D106.1, D107.1, D108.1, D109.1, D110.1, D111.1, D112.1, PAIR07.3
ROW_07_A: D113.1, D114.1, D115.1, D116.1, D117.1, D118.1, D119.1, D120.1, D121.1, D122.1, D123.1, D124.1, D125.1, D126.1, D127.1, D128.1, PAIR08.3
ROW_08_A: D129.1, D130.1, D131.1, D132.1, D133.1, D134.1, D135.1, D136.1, D137.1, D138.1, D139.1, D140.1, D141.1, D142.1, D143.1, D144.1, PAIR09.3
ROW_09_A: D145.1, D146.1, D147.1, D148.1, D149.1, D150.1, D151.1, D152.1, D153.1, D154.1, D155.1, D156.1, D157.1, D158.1, D159.1, D160.1, PAIR10.3
ROW_10_A: D161.1, D162.1, D163.1, D164.1, D165.1, D166.1, D167.1, D168.1, D169.1, D170.1, D171.1, D172.1, D173.1, D174.1, D175.1, D176.1, PAIR11.3
ROW_11_A: D177.1, D178.1, D179.1, D180.1, D181.1, D182.1, D183.1, D184.1, D185.1, D186.1, D187.1, D188.1, D189.1, D190.1, D191.1, D192.1, PAIR12.3
ROW_12_A: D193.1, D194.1, D195.1, D196.1, D197.1, D198.1, D199.1, D200.1, D201.1, D202.1, D203.1, D204.1, D205.1, D206.1, D207.1, D208.1, PAIR13.3
ROW_13_A: D209.1, D210.1, D211.1, D212.1, D213.1, D214.1, D215.1, D216.1, D217.1, D218.1, D219.1, D220.1, D221.1, D222.1, D223.1, D224.1, PAIR14.3
ROW_14_A: D225.1, D226.1, D227.1, D228.1, D229.1, D230.1, D231.1, D232.1, D233.1, D234.1, D235.1, D236.1, D237.1, D238.1, D239.1, D240.1, PAIR15.3
ROW_15_A: D241.1, D242.1, D243.1, D244.1, D245.1, D246.1, D247.1, D248.1, D249.1, D250.1, D251.1, D252.1, D253.1, D254.1, D255.1, D256.1, PAIR16.3
ROW_A0: R38.1, U2.2, U3.4
ROW_A1: R39.1, U2.3, U3.5
ROW_A2: R40.1, U2.21, U3.6
ROW_A3: R41.1, U2.22, U3.7
ROW_ARM: U54.5, U55.3
ROW_ENABLE_N: R42.2, U2.23
ROW_ENABLE_N_CANDIDATE: TP14.1, U54.3
ROW_ENABLE_REQ_N: R106.2, TP7.1, U3.12, U54.1, U54.2
ROW_GATE_00: PAIR01.5, PAIR01.6, R6.2
ROW_GATE_01: PAIR02.5, PAIR02.6, R7.2
ROW_GATE_02: PAIR03.5, PAIR03.6, R8.2
ROW_GATE_03: PAIR04.5, PAIR04.6, R9.2
ROW_GATE_04: PAIR05.5, PAIR05.6, R10.2
ROW_GATE_05: PAIR06.5, PAIR06.6, R11.2
ROW_GATE_06: PAIR07.5, PAIR07.6, R12.2
ROW_GATE_07: PAIR08.5, PAIR08.6, R13.2
ROW_GATE_08: PAIR09.5, PAIR09.6, R14.2
ROW_GATE_09: PAIR10.5, PAIR10.6, R15.2
ROW_GATE_10: PAIR11.5, PAIR11.6, R16.2
ROW_GATE_11: PAIR12.5, PAIR12.6, R17.2
ROW_GATE_12: PAIR13.5, PAIR13.6, R18.2
ROW_GATE_13: PAIR14.5, PAIR14.6, R19.2
ROW_GATE_14: PAIR15.5, PAIR15.6, R20.2
ROW_GATE_15: PAIR16.5, PAIR16.6, R21.2
ROW_REQUEST: U54.6, U54.7
ROW_SEL_00: PAIR01.2, R22.1, U2.11
ROW_SEL_01: PAIR02.2, R23.1, U2.9
ROW_SEL_02: PAIR03.2, R24.1, U2.10
ROW_SEL_03: PAIR04.2, R25.1, U2.8
ROW_SEL_04: PAIR05.2, R26.1, U2.7
ROW_SEL_05: PAIR06.2, R27.1, U2.6
ROW_SEL_06: PAIR07.2, R28.1, U2.5
ROW_SEL_07: PAIR08.2, R29.1, U2.4
ROW_SEL_08: PAIR09.2, R30.1, U2.18
ROW_SEL_09: PAIR10.2, R31.1, U2.17
ROW_SEL_10: PAIR11.2, R32.1, U2.20
ROW_SEL_11: PAIR12.2, R33.1, U2.19
ROW_SEL_12: PAIR13.2, R34.1, U2.14
ROW_SEL_13: PAIR14.2, R35.1, U2.13
ROW_SEL_14: PAIR15.2, R36.1, U2.16
ROW_SEL_15: PAIR16.2, R37.1, U2.15
SYS_I2C_SCL: R80.2, TP12.1, U3.11, U46.7
SYS_I2C_SDA: R79.2, TP11.1, U3.10, U46.6
TEMP_OK: R91.2, U39.4, U39.6, U40.1
TMP_COLD_SET: R90.1, U39.2
TMP_HOT_SET: R89.1, U39.1
UART0_RX: TP5.1, U3.36
UART0_TX: R47.2, TP4.1
UART0_TX_RAW: R47.1, U3.37
USB_CC1: J1.A5, U31.1, U33.4
USB_CC2: J1.B5, U31.2, U33.5
USB_CC_HIGH: U11.4, U17.6
USB_CHARGE_REQ: TP30.1, U17.4, U23.2, U42.1
USB_CONN_DM: J1.A7, J1.B7, U32.5, U33.2
USB_CONN_DP: J1.A6, J1.B6, U32.3, U33.1
USB_D+: R46.2, U32.2
USB_D-: R45.2, U32.6
USB_DN_MCU: R45.1, U3.13
USB_DP_MCU: R46.1, U3.14
USB_EN1_RAW_N: R70.2, TP31.1, U23.4
USB_LOGIC_CT: R77.2, U34.4
USB_LOGIC_READY: U17.3, U25.4
USB_LOGIC_SENSE: R75.2, R76.1, U34.5
USB_OUT1: U11.2, U24.6
USB_OUT2: TP21.1, U24.4
USB_RAW_LOGIC_READY: R63.1, R78.2, TP23.1, U25.3, U34.1, U43.1
USB_RAW_OUT1: R60.1, TP20.1, U24.1, U31.7
USB_RAW_OUT2: R61.1, U24.3, U31.8
USB_RAW_VBUS_VALID: R62.1, TP22.1, U25.1
USB_VBUS_DET: R71.2, U31.4
USB_VBUS_VALID: U17.1, U25.6
VBUS_CONNECTOR: C60.1, J1.A4_B9, J1.B4_A9, R71.1, R97.1, R99.1, TP32.1, U45.5
VLED: C46.1, C47.1, C48.1, C49.1, PAIR01.4, PAIR02.4, PAIR03.4, PAIR04.4, PAIR05.4, PAIR06.4, PAIR07.4, PAIR08.4, PAIR09.4, PAIR10.4, PAIR11.4, PAIR12.4, PAIR13.4, PAIR14.4, PAIR15.4, PAIR16.4, R6.1, R7.1, R8.1, R9.1, R10.1, R11.1, R12.1, R13.1, R14.1, R15.1, R16.1, R17.1, R18.1, R19.1, R20.1, R21.1, R84.1, R109.1, R111.1, R113.1, U37.4, U37.5
VLED_ENABLE_CANDIDATE: TP13.1, U55.7
VLED_ENABLE_DRAFT: R87.1, U37.12
VLED_FB: R85.2, R86.1, U37.3
VLED_FB_TOP_MID: R84.2, R85.1
VLED_HIGH_SENSE: R111.2, R112.1, U53.3
VLED_LOW_SENSE: R109.2, R110.1, U53.4
VLED_WINDOW_OK: R104.2, U53.1, U53.6, U55.6

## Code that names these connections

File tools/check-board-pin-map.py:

#!/usr/bin/env python3
# SPDX-License-Identifier: Apache-2.0
"""Derive/check a provisional U3 pin inventory; never configures hardware."""
import argparse
from collections import Counter
import hashlib
import json
from pathlib import Path
import re
import runpy
import sys
import xml.etree.ElementTree as ET

TOOLS = Path(__file__).resolve().parent
ROOT = TOOLS.parent
CHECK = runpy.run_path(str(TOOLS / "check-coupon-controller.py"))
PROJECT = CHECK["PROJECT"]
DEFAULT_MANIFEST = ROOT / "firmware/boards/coupon-rev-a.json"
DATASHEET = {
    "url": "https://documentation.espressif.com/esp32-s3-wroom-1_wroom-1u_datasheet_en.pdf",
    "version": "1.8",
    "sha256": "27d71971da07c280c6068d08c74720d1a25b8f20cf8494dc1765bdd28d40d435",
    "reviewed_pages": [3, 10, 11, 12, 13],
    "reviewed_on": "2026-10-21",
}
BOUNDARIES = [
    {"ref": "U3", "pin": "12", "net": "ROW_ENABLE_REQ_N"},
    {"ref": "U2", "pin": "23", "net": "ROW_ENABLE_N"},
    {"ref": "U3", "pin": "17", "net": "DISPLAY_ENABLE"},
    {"ref": "TP13", "pin": "1", "net": "VLED_ENABLE_CANDIDATE"},
    {"ref": "TP14", "pin": "1", "net": "ROW_ENABLE_N_CANDIDATE"},
]


def sha(path):
    return hashlib.sha256(Path(path).read_bytes()).hexdigest()


def require(condition, message):
    if not condition:
        raise ValueError(message)


def derive(project=PROJECT):
    connections = CHECK["check_sources"](project)
    controller = CHECK["parse"](project / "controller.kicad_sch")
    instance = next(s for s in CHECK["children"](controller, "symbol") if CHECK["props"](s)["Reference"] == "U3")
    properties = CHECK["props"](instance)
    require(properties.get("Manufacturer") == "Espressif Systems", "Source U3 manufacturer differs")
    require(properties.get("Datasheet") == DATASHEET["url"], "Source U3 datasheet identity differs")
    lib = CHECK["LIB"]
    symbols = {s[1]: s for s in lib["children"](lib["parse"](project / "symbols/rgb-badge-coupon.kicad_sym"), "symbol")}
    mpn, _, footprint = CHECK["PARTS"]["U3"]
    module = lib["library_pins"](symbols[mpn])
    lands = lib["children"](lib["footprint"](project, "ESP32-S3-WROOM-1U"), "pad")
    multiplicity = Counter(pad[1] for pad in lands)
    pins = []
    for number in range(1, 42):
        key = str(number)
        pin = module[key]
        symbol_name = lib["one"](pin, "name", "module pin")[1]
        match = re.match(r"GPIO([0-9]+)(?:/|$)", symbol_name)
        gpio = int(match[1]) if match else None
        manufacturer_name = ("RXD0" if gpio == 44 else "TXD0" if gpio == 43 else
                             f"IO{gpio}" if gpio is not None else "EPAD" if number == 41 else symbol_name)
        net = connections.get(("U3", key))
        pins.append({
            "module_pin": number, "manufacturer_name": manufacturer_name,
            "symbol_name": symbol_name, "electrical_type": pin[1], "gpio": gpio,
            "net": net, "explicit_no_connect": key in CHECK["MODULE_NC"],
            "physical_land_count": multiplicity[key],
            "strapping_pin": gpio in (0, 3, 45, 46),
            "reserved_for_octal_psram": gpio in (35, 36, 37),
        })
    require(len({p["gpio"] for p in pins if p["gpio"] is not None}) == 36, "GPIO identities are not unique")
    require(all(p["explicit_no_connect"] and p["net"] is None for p in pins if p["reserved_for_octal_psram"]),
            "Octal PSRAM pins must remain unconnected")
    canonical = sorted(project.glob("*.kicad_sch"))
    canonical += [project / "symbols/rgb-badge-coupon.kicad_sym",
                  project / "footprints/rgb-badge-coupon.pretty/ESP32-S3-WROOM-1U.kicad_mod"]
    return {
        "SPDX-License-Identifier": "Apache-2.0", "schema_version": 1,
        "hardware_revision": "coupon-rev-a", "status": "PROVISIONAL_NOT_FROZEN",
        "production_gpio_configuration_allowed": False,
        "canonical_project": "hardware/coupon/rev-a/rgb-badge-coupon.kicad_pro",
        "controller_reference": "U3", "manufacturer": "Espressif Systems",
        "manufacturer_part_number": mpn, "footprint": footprint,
        "manufacturer_source": DATASHEET,
        "canonical_source_sha256": {str(p.relative_to(project)): sha(p) for p in canonical},
        "generation_tool_sha256": {p.name: sha(p) for p in (
            Path(__file__), TOOLS / "check-coupon-controller.py", TOOLS / "check-controller-libraries.py")},
        "required_native_boundaries": BOUNDARIES, "pins": pins,
    }


def render(document):
    return json.dumps(document, indent=2, sort_keys=True, allow_nan=False) + "\n"


def unique_object(pairs):
    result = {}
    for key, value in pairs:
        require(key not in result, f"Duplicate JSON key: {key}")
        result[key] = value
    return result


def check_manifest(path, expected):
    text = path.read_text()
    document = json.loads(text, object_pairs_hook=unique_object)
    require(render(document) == render(expected), "Pin inventory/source metadata differs; review then regenerate")
    require(text == render(expected), "Pin inventory serialization differs; regenerate deterministically")


def check_native(path, document):
    # Independent native export must also satisfy the entire existing coupon contract.
    CHECK["check_netlist"](path)
    root = ET.parse(path).getroot()
    modules = root.findall("./components/comp[@ref='U3']")
    require(len(modules) == 1, "Expected one native U3")
    module = modules[0]
    mpn = document["manufacturer_part_number"]
    require(module.findtext("value") == mpn and module.findtext("footprint") == document["footprint"],
            "Native U3 part/footprint differs")
    require(module.findtext("./fields/field[@name='MPN']") == mpn, "Native U3 exact MPN field differs")
    require(module.findtext("./fields/field[@name='Manufacturer']") == document["manufacturer"],
            "Native U3 manufacturer differs")
    require(module.findtext("datasheet") == document["manufacturer_source"]["url"], "Native U3 datasheet differs")
    source = module.find("libsource")
    require(source is not None and source.get("lib") == "rgb-badge-coupon" and source.get("part") == mpn,
            "Native U3 library identity differs")
    native = {}
    for net in root.findall("./nets/net"):
        for node in net.findall("node"):
            key = (node.get("ref"), node.get("pin"))
            require(key not in native, f"Duplicate native pin: {key}")
            native[key] = (net.get("name"), node)
    require({pin for ref, pin in native if ref == "U3"} == {str(p["module_pin"]) for p in document["pins"]},
            "Native U3 pin inventory differs")
    for pin in document["pins"]:
        number = str(pin["module_pin"])
        net, node = native["U3", number]
        expected_net = (f"unconnected-(U3-{pin['symbol_name']}-Pad{number})"
                        if pin["explicit_no_connect"] else pin["net"])
        require(net == expected_net, f"Native U3.{number} net differs")
        require(node.get("pinfunction") == f"{pin['symbol_name']}_{number}", f"Native U3.{number} function differs")
        expected_type = pin["electrical_type"] + ("+no_connect" if pin["explicit_no_connect"] else "")
        require(node.get("pintype") == expected_type, f"Native U3.{number} electrical/NC type differs")
    for boundary in document["required_native_boundaries"]:
        key = boundary["ref"], boundary["pin"]
        require(key in native and native[key][0] == boundary["net"], f"Native display boundary differs: {key}")


def main():
    parser = argparse.ArgumentParser(description=__doc__)
    parser.add_argument("--project-dir", type=Path, default=PROJECT)
    parser.add_argument("--manifest", type=Path, default=DEFAULT_MANIFEST)
    parser.add_argument("--write", action="store_true", help="Regenerate derived JSON after source review")
    parser.add_argument("--netlist", type=Path, help="Also check a complete native KiCad XML export")
    args = parser.parse_args()
    try:
        document = derive(args.project_dir)
        if args.netlist:
            check_native(args.netlist, document)
        if args.write:
            args.manifest.parent.mkdir(parents=True, exist_ok=True)
            args.manifest.write_text(render(document))
        else:
            check_manifest(args.manifest, document)
        print("Coupon pin inventory passed: 41 module pins, 36 GPIO identities, 25 connected / 16 explicit NC; PROVISIONAL.")
        if args.netlist:
            print("Complete native XML and module pin/function/type/MPN/display-boundary checks passed.")
        return 0
    except (OSError, ValueError, KeyError, IndexError, ET.ParseError) as error:
        print(f"Pin inventory check failed: {error}", file=sys.stderr)
        return 1


if __name__ == "__main__":
    sys.exit(main())

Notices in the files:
parts and their libraries:
GCT USB4505 A2 2023-12-18; 0.80mm PCB; cutout relief/process confirmation pending; SPDX-License-Identifier: CERN-OHL-S-2.0
Manufacturer range-based reflow land pattern; SPDX-License-Identifier: CERN-OHL-S-2.0
TI DBZ0003A SOT-23-3 example land pattern; SPDX-License-Identifier: CERN-OHL-S-2.0
